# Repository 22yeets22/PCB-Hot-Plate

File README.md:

<h1 align="center">
  PCB Hot Plate
  <br>
</h1>

<h4 align="center">
A 140W universal USB-C powered PCB Hot Plate!
</h4>
<br>

<div align="center">

| Controller                                     | Heating Element                                      |
| ---------------------------------------------- | ---------------------------------------------------- |
|  |  |

</div>

## Description

A 140W USB-C-powered PCB hot plate for precise heating, such as for solder reflow. It uses a USB-C power input for accessibility and uses an aluminium PCB heating element driven a switching MOSFET, along with thermistors to monitor temperature, USB-C negotiation, and real-time current/voltage monitoring.

## Motivation

My motivation for this project was to create a low-cost, customizable, fully controllable PCB hotplate for electronics work, like soldering or heating stuff up. I thought that other hotplates online were very expensive and lacked the power I wanted. By designing a custom solution, I made a new hot plate capable of higher wattage (140W) and better flexibility.

## Features

- Powered by the pi pico
- Supports 140W (28V, 5A) from USB-C
- Compatible with any usb-c device
- 1.8 inch LCD screen
- 4 buttons to control
- LEDS for visualization
- Seperated heating element and controller for ease of replacement
- Temperature control

## BOM

| Name                                                                                                       | Purpose                                                      | Quantity | Total Cost (USD) | Link                                                 | Distributor               |
| ---------------------------------------------------------------------------------------------------------- | ------------------------------------------------------------ | -------- | ---------------- | ---------------------------------------------------- | ------------------------- |
| 1.8in LCD Screen                                                                                           | See navigation + temp + UI                                   | 1        | 3.79             | https://www.aliexpress.us/item/3256811557250210.html | Aliexpress                |
| 2.54mm Pin Headers - Male                                                                                  | Fill in the 1x6 and the 1x4 pin headers                      | 1        | 4.19             | https://www.aliexpress.us/item/3256806547306536.html | Aliexpress                |
| 2.54mm Pin Headers - Female                                                                                | Breakaway headers to fill in the 1x8 spot for the LCD Screen | 1        | 4.66             | https://www.aliexpress.us/item/3256806547306536.html | Aliexpress                |
| PCB Heating Element                                                                                        | The actual heating element to heat it up.                    | 10       | 5.00             |                                                      | JLCPCB                    |
| Controller PCB                                                                                             | The actual fr-4 pcb to control all of this                   | 10       | 5.00             |                                                      | JLCPCB                    |
| Diode Independent 40V 3A Surface Mount SMA(DO-214AC)                                                       |                                                              | 20       | 0.66             |                                                      | GOODWORK                  |
| 1uF ±10% 50V Ceramic Capacitor X5R 0603                                                                    |                                                              | 50       | 0.39             |                                                      | Samsung Electro-Mechanics |
| 100nF ±10% 50V Ceramic Capacitor X7R 0603                                                                  |                                                              | 100      | 0.31             |                                                      | YAGEO                     |
| 22uF ±20% 35V Aluminum Electrolytic Capacitors 2000hrs@105℃                                                |                                                              | 40       | 1.28             |                                                      | KNSCHA                    |
| 49.9kΩ ±1% 100mW 0603 Thick Film Resistor                                                                  |                                                              | 100      | 0.15             |                                                      | UNI-ROYAL                 |
| 100uF ±20% 35V Aluminum Electrolytic Capacitors 2800hrs@105℃                                               |                                                              | 20       | 0.78             |                                                      | DMBJ                      |
| 5pA 2 2V/us 1MHz Rail-to-Rail Input, Rail-to-Rail Output SOIC-8 Instrumentation, Op Amps, Buffer Amps RoHS |                                                              | 10       | 1.18             |                                                      | TI                        |
| Buck Switching Regulator IC Adjustable 0.8V~24V 1 Output 2A SOP-8-EP                                       |                                                              | 10       | 1.19             |                                                      | GATEMODE                  |
| 5V~18V 1.5A SOIC-8 Gate Drivers RoHS                                                                       |                                                              | 10       | 3.12             |                                                      | Tokmas                    |
| 3A 6.8uH ±20% 40mΩ 3.3A Magnetic Shielded Inductor SMD,6x6mm                                               |                                                              | 10       | 0.37             |                                                      | GUDIAN                    |
| 100mW 56kΩ 75V Thick Film Resistor ±1% 0603                                                                |                                                              | 100      | 0.16             |                                                      | YAGEO                     |
| 210kΩ ±1% 100mW 0603 Thick Film Resistor                                                                   |                                                              | 100      | 0.15             |                                                      | UNI-ROYAL                 |
| 82kΩ ±1% 100mW 0603 Thick Film Resistor                                                                    |                                                              | 100      | 0.11             |                                                      | FOJAN                     |
| 100mW 1kΩ 75V Thick Film Resistor ±1% 0603                                                                 |                                                              | 100      | 0.15             |                                                      | YAGEO                     |
| 10mΩ 1W ±1% 1206 Chip Resistor                                                                             |                                                              | 10       | 0.47             |                                                      | JIERR                     |
| 10Ω ±1% 100mW 0603 Thick Film Resistor                                                                     |                                                              | 100      | 0.10             |                                                      | FOJAN                     |
| 100mW 10kΩ 75V Thick Film Resistor ±1% 0603                                                                |                                                              | 100      | 0.15             |                                                      | YAGEO                     |
| 5.1kΩ ±1% 100mW 0603 Thick Film Resistor                                                                   |                                                              | 100      | 0.12             |                                                      | FOJAN                     |
| 100mW 330Ω 75V Thick Film Resistor ±1% 0603                                                                |                                                              | 100      | 0.15             |                                                      | YAGEO                     |
| P-Channel 40V 25A Surface Mount PDFN5060-8L                                                                |                                                              | 10       | 1.06             |                                                      | XNRUSEMI                  |
| N-Channel 40V 10A Surface Mount SOP-8                                                                      |                                                              | 10       | 0.77             |                                                      | XNRUSEMI                  |
| 10A 22uH ±20% SMD Inductor                                                                                 |                                                              | 10       | 3.22             |                                                      | XR                        |
| Tactile Switch SPST 180gf 6mm x 6mm SMD                                                                    |                                                              | 40       | 2.28             |                                                      | Yuandi                    |
| Female Header 20 Position 2.54mm Pitch                                                                     |                                                              | 20       | 2.25             |                                                      | HanElectricity            |
| USB-C Receptacle Connector 16 Position SMD                                                                 |                                                              | 10       | 1.85             |                                                      | Korean Hroparts Elec      |
| Zener Diode 15V 500mW SOD-123                                                                              |                                                              | 50       | 0.73             |                                                      | MDD                       |
| Emerald Green LED 0603                                                                                     |                                                              | 100      | 0.61             |                                                      | YONGYUTAI                 |

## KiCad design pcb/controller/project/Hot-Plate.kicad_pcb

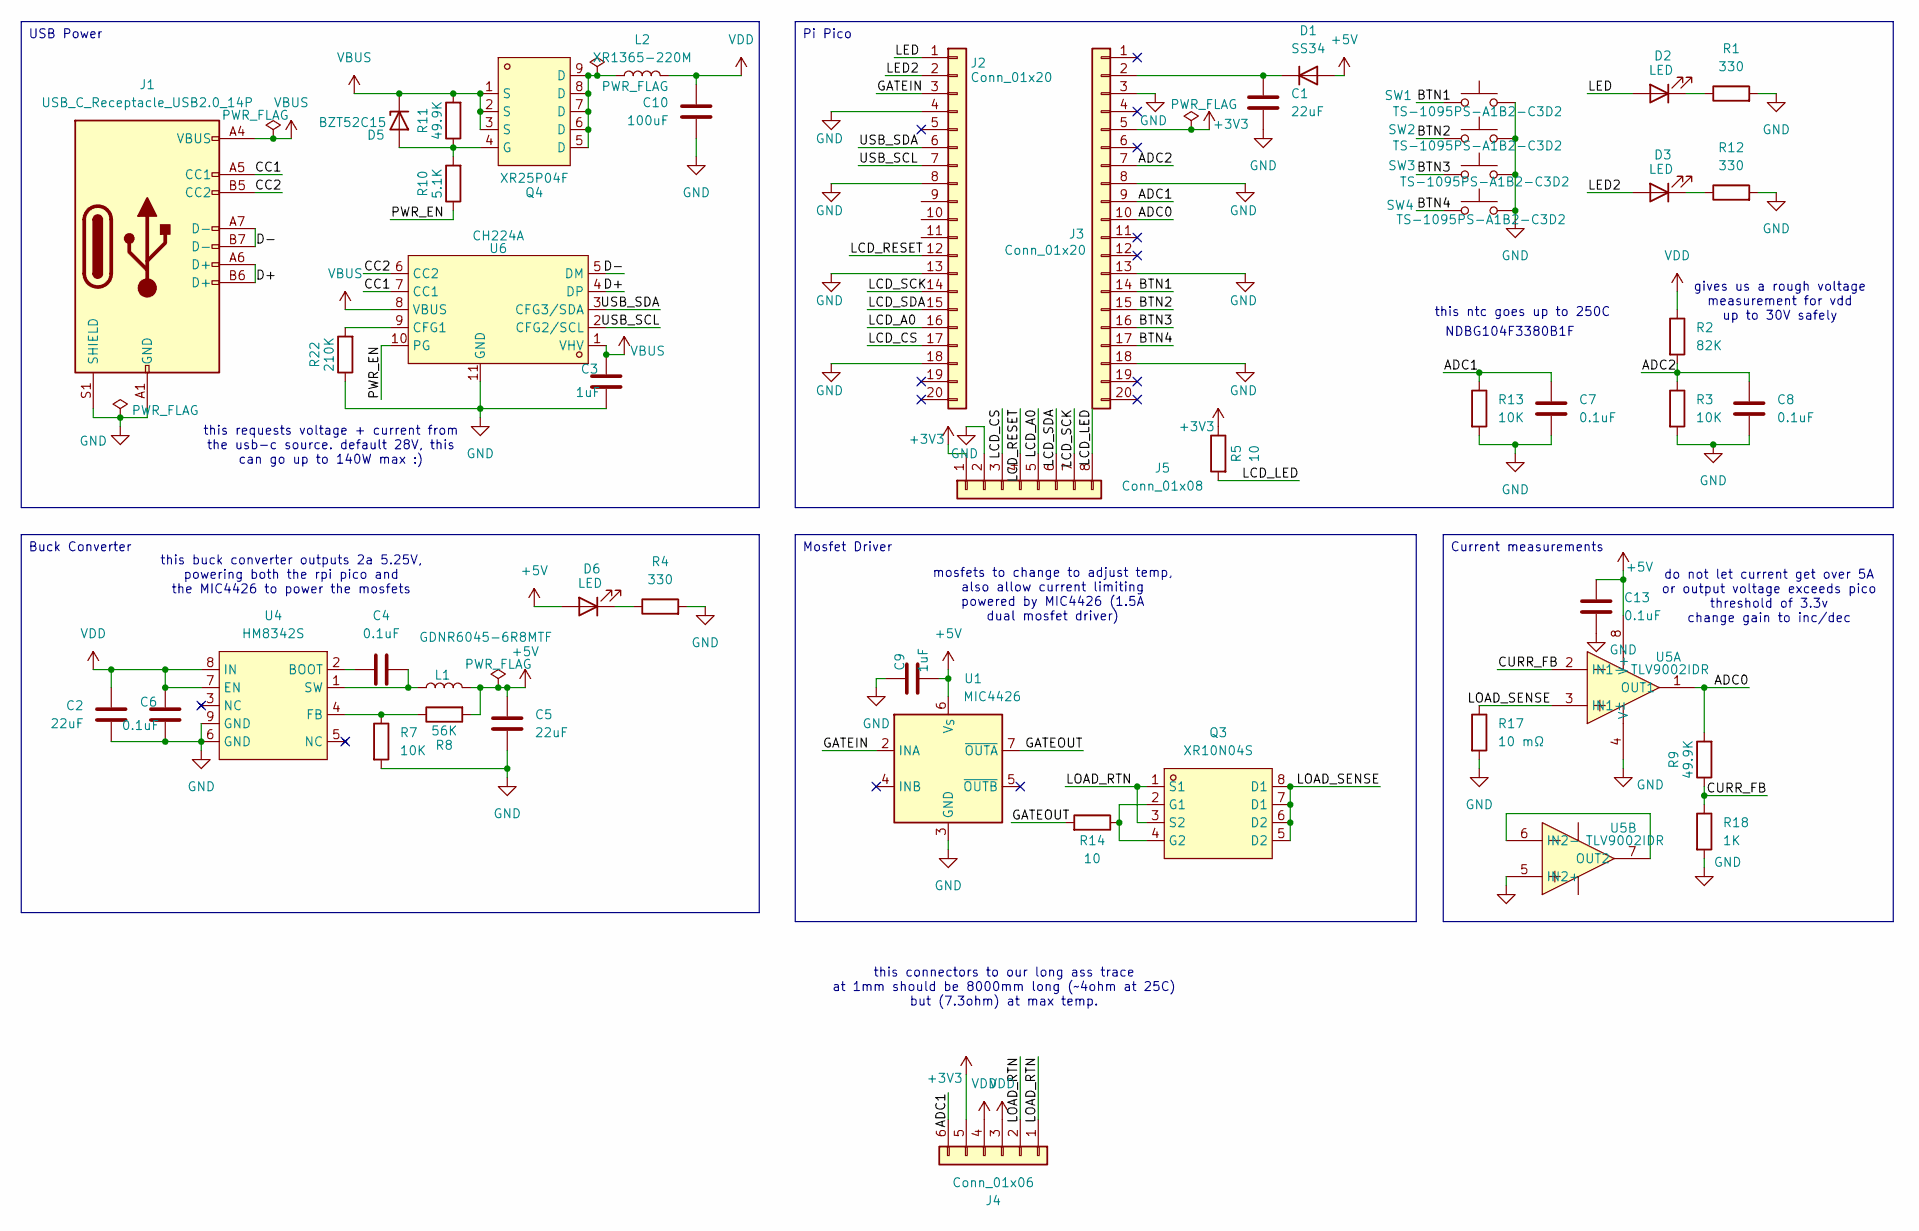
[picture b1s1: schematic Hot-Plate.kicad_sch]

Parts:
C1, C2, C5: 22uF; CP_Elec_5x5.4
C3, C9: 1uF; C_0603_1608Metric_Pad1.08x0.95mm_HandSolder
C4, C6, C7, C8, C13: 0.1uF; C_0603_1608Metric_Pad1.08x0.95mm_HandSolder
C10: 100uF; CP_Elec_6.3x7.7
D1: SS34; D_SMA_Handsoldering
D2, D3, D6: LED; LED_0603_1608Metric_Pad1.05x0.95mm_HandSolder
D5: BZT52C15; D_SOD-123
J1: USB_C_Receptacle_USB2.0_14P; USB_C_Receptacle_GCT_USB4105-xx-A_16P_TopMnt_Horizontal
J2, J3: Conn_01x20; PinSocket_1x20_P2.54mm_Vertical
J4: Conn_01x06; PinHeader_1x06_P2.54mm_Vertical
J5: Conn_01x08; PinSocket_1x08_P2.54mm_Vertical
L1: GDNR6045-6R8MTF; L_6.3x6.3_H3
L2: XR1365-220M; IND-SMD_L13.5-W12.6_YSPI1335T-1R0M
Q3: XR10N04S; SOP-8_L4.9-W3.9-P1.27-LS6.0-BL; MPN XR10N04S; LCSC Part C42456793
Q4: XR25P04F; PDFN-8_L5.8-W5.0-P1.27-LS6.1-BL; MPN XR25P04F; LCSC Part C42456987
R1, R4, R12: 330; R_0603_1608Metric_Pad0.98x0.95mm_HandSolder
R2: 82K; R_0603_1608Metric_Pad0.98x0.95mm_HandSolder
R3, R7, R13: 10K; R_0603_1608Metric_Pad0.98x0.95mm_HandSolder
R5, R14: 10; R_0603_1608Metric_Pad0.98x0.95mm_HandSolder
R8: 56K; R_0603_1608Metric_Pad0.98x0.95mm_HandSolder
R9, R11: 49.9K; R_0603_1608Metric_Pad0.98x0.95mm_HandSolder
R10: 5.1K; R_0603_1608Metric_Pad0.98x0.95mm_HandSolder
R17: 10 mΩ; R_1206_3216Metric_Pad1.30x1.75mm_HandSolder
R18: 1K; R_0603_1608Metric_Pad0.98x0.95mm_HandSolder
R22: 210K; R_0603_1608Metric_Pad0.98x0.95mm_HandSolder
SW1, SW2, SW3, SW4: TS-1095PS-A1B2-C3D2; KEY-SMD_4P-L6.0-W6.0-P3.90-LS9.0
U1: MIC4426; SOIC-8_L4.9-W3.9-P1.27-LS6.0-BL
U4: HM8342S; ESOP-8_L4.9-W3.9-P1.27-LS6.0-BL-EP-1; MPN HM8342S; LCSC Part C46634661
U5: TLV9002IDR; SOIC-8_L4.9-W3.9-P1.27-LS6.0-BL; MPN TLV9002IDR; LCSC Part C398360
U6: CH224A; ESSOP-10_L4.9-W3.9-P1.0-LS6.0-TL-EP; MPN CH224A; LCSC Part C42459160

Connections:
+3V3: J3.5, J4.5, J5.1, R5.1
+5V: C5.1, C9.2, C13.2, D1.2 (A), D6.2 (A), L1.2, R8.2, U1.6 (V_{S}), U5.8 (V+)
/ADC0: J3.10, R9.2, U5.1 (OUT1)
/ADC1: C7.1, J3.9, J4.6, R13.1
/ADC2: C8.1, J3.7, R2.2, R3.1
/BTN1: J3.14, SW1.1
/BTN2: J3.15, SW2.1
/BTN3: J3.16, SW3.1
/BTN4: J3.17, SW4.1
/CC1: J1.A5 (CC1), U6.7 (CC1)
/CC2: J1.B5 (CC2), U6.6 (CC2)
/CURR_FB: R9.1, R18.1, U5.2 (IN1-)
/D+: J1.A6 (D+), J1.B6 (D+), U6.4 (DP)
/D-: J1.A7 (D-), J1.B7 (D-), U6.5 (DM)
/GATEIN: J2.3, U1.2 (INA)
/GATEOUT: R14.2, U1.7 (~OUTA)
/LCD_A0: J2.16, J5.5
/LCD_CS: J2.17, J5.3
/LCD_LED: J5.8, R5.2
/LCD_RESET: J2.12, J5.4
/LCD_SCK: J2.14, J5.7
/LCD_SDA: J2.15, J5.6
/LED: D2.2 (A), J2.1
/LED2: D3.2 (A), J2.2
/LOAD_RTN: J4.1, J4.2, Q3.1 (S1), Q3.3 (S2)
/LOAD_SENSE: Q3.5 (D2), Q3.6 (D2), Q3.7 (D1), Q3.8 (D1), R17.1, U5.3 (IN1+)
/PWR_EN: R10.1, U6.10 (PG)
/USB_SCL: J2.7, U6.2 (CFG2/SCL)
/USB_SDA: J2.6, U6.3 (CFG3/SDA)
GND: C1.2, C2.2, C3.2, C5.2, C6.2, C7.2, C8.2, C9.1, C10.2, C13.1, J1.A1 (GND), J1.A12 (GND), J1.B1 (GND), J1.B12 (GND), J1.S1 (SHIELD), J2.4, J2.8, J2.13, J2.18, J3.3, J3.8, J3.13, J3.18, J5.2, R1.2, R3.2, R4.2, R7.2, R12.2, R13.2, R17.2, R18.2, R22.1, SW1.2, SW2.2, SW3.2, SW4.2, U1.3 (GND), U4.6 (GND), U4.9 (GND), U5.4 (V-), U5.5 (IN2+), U6.11 (GND)
unnamed: C1.1, D1.1 (K), J3.2
unnamed: D2.1 (K), R1.1
unnamed: D3.1 (K), R12.1
unnamed: D5.2 (A), Q4.4 (G), R10.2, R11.1
unnamed: D6.1 (K), R4.1
unnamed: L2.2, Q4.5 (D), Q4.6 (D), Q4.7 (D), Q4.8 (D), Q4.9 (D)
unnamed: Q3.2 (G1), Q3.4 (G2), R14.1
unnamed: C4.2, U4.2 (BOOT)
unnamed: R7.1, R8.1, U4.4 (FB)
unnamed: C4.1, L1.1, U4.1 (SW)
unnamed: U5.6 (IN2-), U5.7 (OUT2)
unnamed: R22.2, U6.9 (CFG1)
VBUS: C3.1, D5.1 (K), J1.A4 (VBUS), J1.A9 (VBUS), J1.B4 (VBUS), J1.B9 (VBUS), Q4.1 (S), Q4.2 (S), Q4.3 (S), R11.2, U6.1 (VHV), U6.8 (VBUS)
VDD: C2.1, C6.1, C10.1, J4.3, J4.4, L2.1, R2.1, U4.7 (EN), U4.8 (IN)

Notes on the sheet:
this ntc goes up to 250C
do not let current get over 5A or output voltage exceeds pico threshold of 3.3v change gain to inc/dec
this requests voltage + current from the usb-c source. default 28V, this can go up to 140W max :)
NDBG104F3380B1F
this connectors to our long ass trace at 1mm should be 8000mm long (~4ohm at 25C) but (7.3ohm) at max temp.
this buck converter outputs 2a 5.25V, powering both the rpi pico and the MIC4426 to power the mosfets
mosfets to change to adjust temp, also allow current limiting powered by MIC4426 (1.5A dual mosfet driver)
gives us a rough voltage measurement for vdd up to 30V safely
Current measurements
Pi Pico
Buck Converter
USB Power
Mosfet Driver

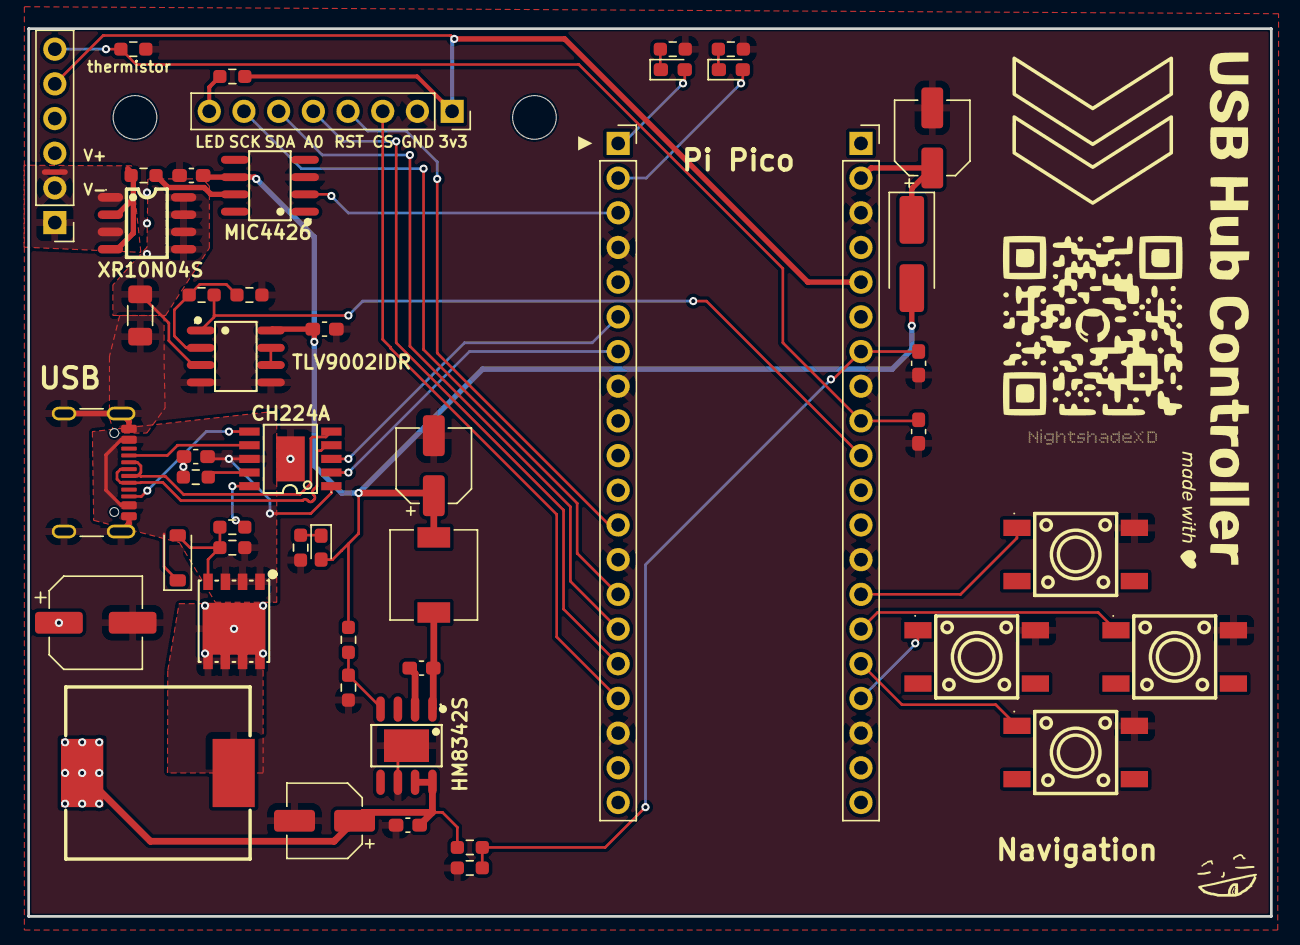
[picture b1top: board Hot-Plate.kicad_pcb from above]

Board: 2 copper layers, 91.0 x 65.0 mm, 49 parts (0 on the bottom side), 44 nets.

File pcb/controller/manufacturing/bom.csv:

Designator,Footprint,Quantity,Value,LCSC Part #
"C1, C2, C5",CP_Elec_5x5.4,3,22uF,
C10,CP_Elec_6.3x7.7,1,100uF,
"C13, C4, C6, C7, C8",0603,5,0.1uF,
"C3, C9",0603,2,1uF,
D1,D_SMA_Handsoldering,1,SS34,
"D2, D3, D6",0603,3,LED,
D5,D_SOD-123,1,BZT52C15,
J1,USB_C_Receptacle_GCT_USB4105-xx-A_16P_TopMnt_Horizontal,1,USB_C_Receptacle_USB2.0_14P,
"J2, J3",PinSocket_1x20_P2.54mm_Vertical,2,Conn_01x20,
J4,PinHeader_1x06_P2.54mm_Vertical,1,Conn_01x06,
J5,PinSocket_1x08_P2.54mm_Vertical,1,Conn_01x08,
L1,L_6.3x6.3_H3,1,GDNR6045-6R8MTF,
L2,IND-SMD_L13.5-W12.6_YSPI1335T-1R0M,1,XR1365-220M,C41384053
Q3,SOP-8_L4.9-W3.9-P1.27-LS6.0-BL,1,XR10N04S,C42456793
Q4,PDFN-8_L5.8-W5.0-P1.27-LS6.1-BL,1,XR25P04F,C42456987
"R1, R12, R4",0603,3,330,
R10,0603,1,5.1K,
"R11, R9",0603,2,50K,
"R13, R3, R7",0603,3,10K,
"R14, R5",0603,2,10,
R17,1206,1,10 mΩ,
R18,0603,1,1K,
R2,0603,1,82K,
R22,0603,1,210K,
R8,0603,1,56K,
"SW1, SW2, SW3, SW4",KEY-SMD_4P-L6.0-W6.0-P3.90-LS9.0,4,TS-1095PS-A1B2-C3D2,C2834918
U1,SOIC-8_L4.9-W3.9-P1.27-LS6.0-BL,1,MIC4426,C398360
U4,ESOP-8_L4.9-W3.9-P1.27-LS6.0-BL-EP-1,1,HM8342S,C46634661
U5,SOIC-8_L4.9-W3.9-P1.27-LS6.0-BL,1,TLV9002IDR,C398360
U6,ESSOP-10_L4.9-W3.9-P1.0-LS6.0-TL-EP,1,CH224A,C42459160

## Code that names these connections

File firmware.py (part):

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ADC2_PIN     = board.GP28   # VDD voltage sense

# Buttons (active low, internal pull-up)
BTN1_PIN     = board.GP18   # Up / scroll up
BTN2_PIN     = board.GP19   # Select / Start
BTN3_PIN     = board.GP20   # Down / scroll down
BTN4_PIN     = board.GP21   # Stop / Back

# LEDs
LED1_PIN     = board.GP0
LED2_PIN     = board.GP1

# SPI / ST7735S LCD
LCD_SCK_PIN  = board.GP10
LCD_SDA_PIN  = board.GP11
LCD_DC_PIN   = board.GP12
LCD_CS_PIN   = board.GP13
LCD_RST_PIN  = board.GP9

# ─────────────────────────────────────────────
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        b.pull = digitalio.Pull.UP
        return b

    hw["btn1"] = make_btn(BTN1_PIN)
    hw["btn2"] = make_btn(BTN2_PIN)
    hw["btn3"] = make_btn(BTN3_PIN)
    hw["btn4"] = make_btn(BTN4_PIN)

    # ── LEDs ─────────────────────────────────
    def make_led(pin):
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        return l

    hw["led1"] = make_led(LED1_PIN)
    hw["led2"] = make_led(LED2_PIN)

    # ── SPI / LCD ────────────────────────────
    displayio.release_displays()
    spi = busio.SPI(clock=LCD_SCK_PIN, MOSI=LCD_SDA_PIN)
    dc  = digitalio.DigitalInOut(LCD_DC_PIN)
    cs  = digitalio.DigitalInOut(LCD_CS_PIN)
    rst = digitalio.DigitalInOut(LCD_RST_PIN)

    display_bus = displayio.FourWire(spi, command=dc, chip_select=cs, reset=rst)
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
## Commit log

2026-04-20 rev1
2026-04-20 untested firmware
